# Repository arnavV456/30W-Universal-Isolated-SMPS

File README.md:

# Universal Isolated SMPS

A **30W isolated AC-DC flyback power supply** designed in **KiCad 9**, capable of converting a universal mains input into regulated isolated DC outputs.

This project implements a complete offline SMPS including EMI filtering, surge protection, isolated feedback, custom transformer footprint creation, PCB layout, 3D visualization, and manufacturing outputs.

---

# PCB Top

---

# PCB Bottom

---

## Specifications

| Parameter | Value |
|-----------|-------|
| Input Voltage | 85–265 VAC |
| Output 1 | 12V @ 2.5A |
| Output Power | 30W |
| Isolation | 4 kV |
| Topology | Flyback |
| Controller IC | TOP244Y |
| Transformer | MYRRA 74030 |
| PCB Layers | 2 |

---

# Features

- Universal AC input (85–265 VAC)
- Fully isolated flyback topology
- Reinforced 4 kV isolation
- TOP244Y integrated PWM controller
- Custom MYRRA 74030 transformer footprint & symbol
- EMI input filter
- MOV surge protection
- Fuse protection
- Common-mode choke
- X-Class capacitor
- Y-Class safety capacitor
- Primary RCD snubber network
- Secondary RC snubber
- Schottky output rectification
- Auxiliary transformer winding for controller bias
- Optocoupler-based isolated voltage feedback
- LC output filtering
- High-current PCB routing
- Separate primary and secondary ground planes
- 3D PCB model
- Manufacturing-ready Gerber generation

---

# Functional Overview

### AC Input Stage
- Universal AC input
- Fuse protection
- MOV surge suppressor
- Common-mode choke
- X and Y safety capacitors for EMI suppression

### High Voltage DC Bus
- Full bridge rectifier
- Bulk electrolytic capacitor for DC filtering

### Flyback Converter
- TOP244Y offline switching controller
- MYRRA 74030 flyback transformer
- Auxiliary winding for self-powered operation

### Protection Networks
- Primary RCD snubber to clamp transformer leakage spikes
- Secondary RC snubber to reduce ringing and EMI

### Output Stage
- MBR1060 Schottky rectifier
- LC output filter
- Low ripple 12V output

### Feedback Network
- LTV817A optocoupler
- Zener reference network
- Closed-loop isolated voltage regulation

### Additional Output
- Buck converter generating regulated 5V rail from the 12V output

---

# PCB Design Highlights

- Two-layer PCB
- Custom transformer footprint
- Custom transformer schematic symbol
- Wide power traces for high-current paths
- Dedicated primary HV_RETURN copper pour
- Dedicated secondary return plane
- Isolation barrier between primary and secondary
- Creepage and clearance maintained across isolation boundary
- Optimized placement for reduced switching loop area

---

# Schematic

---

# Repository Structure

```
Hardware/
├── universal_30w_smps.kicad_pro
├── universal_30w_smps.kicad_sch
├── universal_30w_smps.kicad_pcb
└── MYRRA.pretty/

Manufacturing/
├── Gerbers
└── Drill Files

Images/
├── PCB_Front.png
├── PCB_Back.png
└── schematic.png

3D Models/

README.md
```

---

# Design Tools

- KiCad 9
- Custom KiCad Libraries
- Git & GitHub

---

# Future Improvements

- Thermal analysis
- Efficiency characterization
- EMI compliance testing
- Hardware validation
- Oscilloscope waveform measurements
- Short-circuit and overload testing

---

## Author

**Arnav Verma**

Electronics & Computer Engineering

Embedded Systems • PCB Design • Power Electronics • IoT • STM32 • ESP32

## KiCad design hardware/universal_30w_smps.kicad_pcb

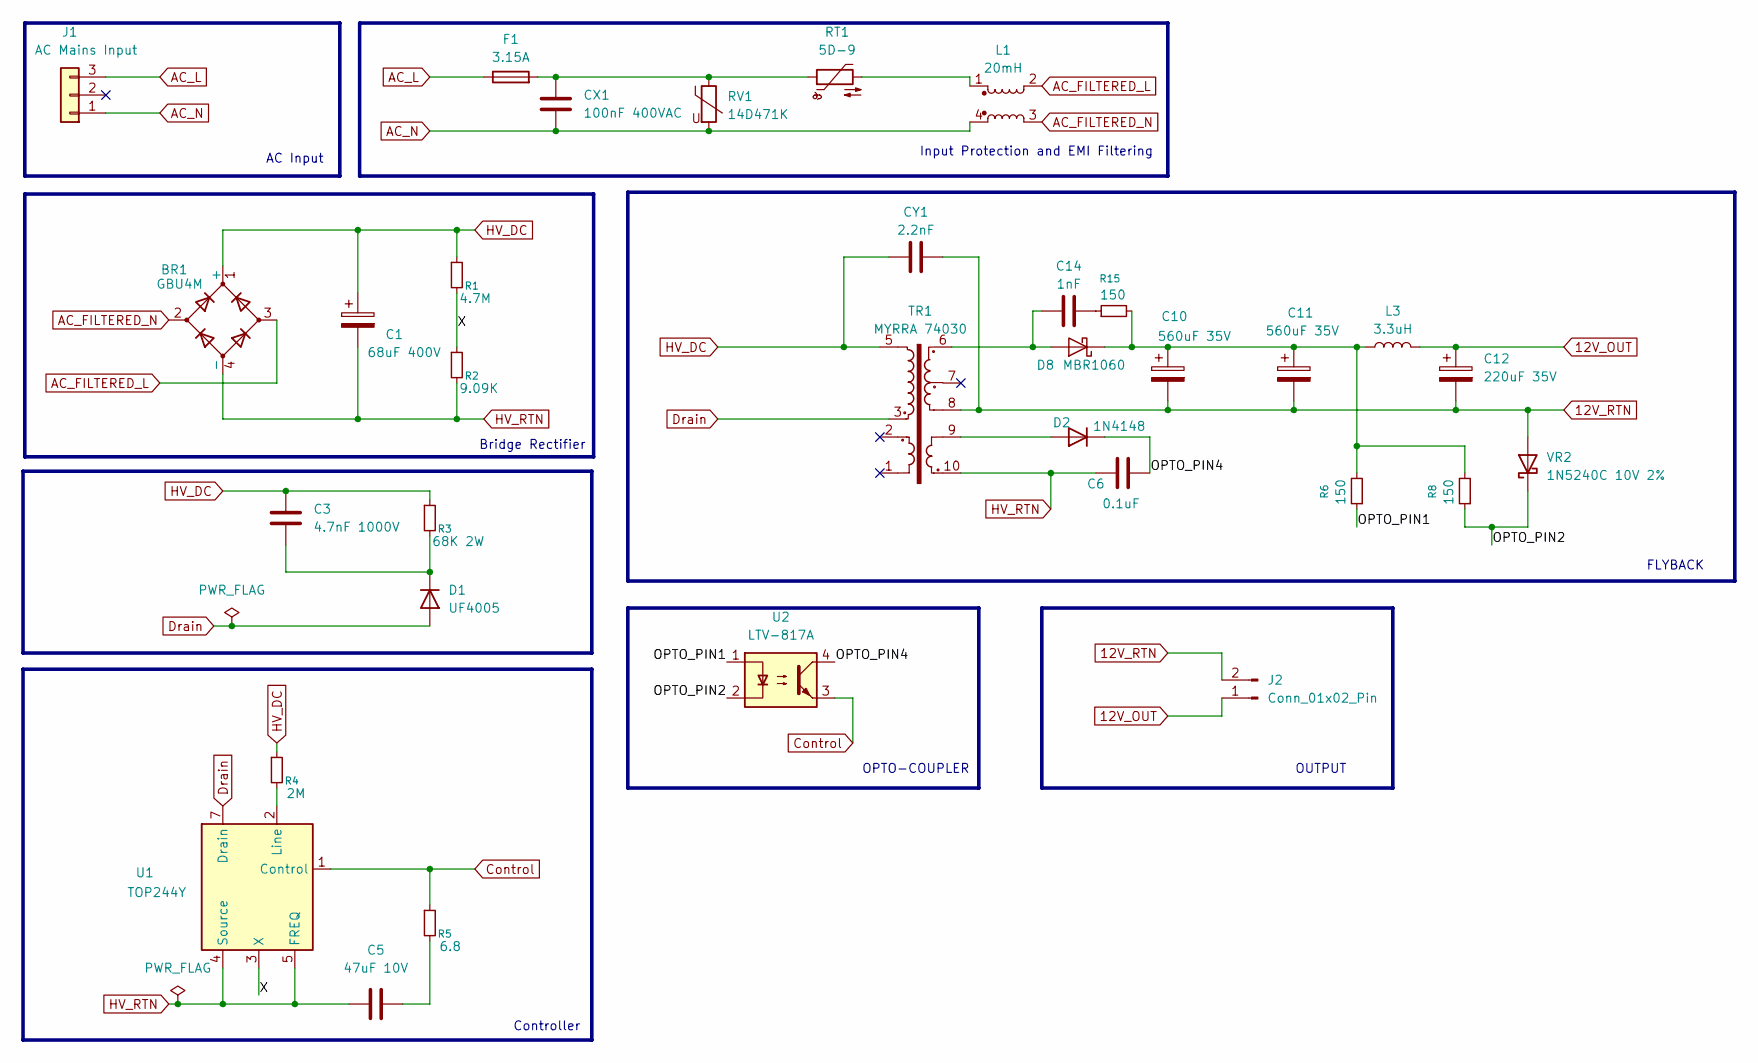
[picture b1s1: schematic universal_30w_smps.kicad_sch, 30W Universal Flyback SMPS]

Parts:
BR1: GBU4M; Diode_Bridge_Vishay_GBU
C1: 68uF 400V; CP_Radial_D18.0mm_P7.50mm
C3: 4.7nF 1000V; C_Rect_L11.0mm_W4.2mm_P10.00mm_MKT
C5: 47uF 10V; C_Radial_D6.3mm_H5.0mm_P2.50mm
C6: 0.1uF; C_Disc_D5.0mm_W2.5mm_P5.00mm
C10, C11: 560uF 35V; C_Disc_D5.0mm_W2.5mm_P5.00mm
C12: 220uF 35V; C_Radial_D10.0mm_H20.0mm_P5.00mm
C14: 1nF; C_Disc_D5.0mm_W2.5mm_P5.00mm
CX1: 100nF 400VAC; C_Rect_L18.0mm_W11.0mm_P15.00mm_FKS3_FKP3
CY1: 2.2nF; C_Disc_D7.5mm_W5.0mm_P10.00mm
D1: UF4005; D_DO-41_SOD81_P10.16mm_Horizontal
D2: 1N4148; D_DO-35_SOD27_P7.62mm_Horizontal
D8: MBR1060; D_SOD-123F
F1: 3.15A; Fuseholder_Cylinder-5x20mm_Stelvio-Kontek_PTF78_Horizontal_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
J1: AC Mains Input; TerminalBlock_Phoenix_MKDS-1,5-3-5.08_1x03_P5.08mm_Horizont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
J2: Conn_01x02_Pin; TerminalBlock_Phoenix_MKDS-1,5-2-5.08_1x02_P5.08mm_Horizont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
L1: 20mH; L_CommonModeChoke_Bourns_SRF1260
L3: 3.3uH; L_Radial_D10.0mm_P5.00mm_Fastron_07P
R1: 4.7M; R_Axial_DIN0207_L6.3mm_D2.5mm_P10.16mm_Horizontal
R2: 9.09K; R_Axial_DIN0207_L6.3mm_D2.5mm_P10.16mm_Horizontal
R3: 68K 2W; R_Axial_DIN0414_L11.9mm_D4.5mm_P15.24mm_Horizontal
R4: 2M; R_Axial_DIN0207_L6.3mm_D2.5mm_P10.16mm_Horizontal
R5: 6.8; R_Axial_DIN0207_L6.3mm_D2.5mm_P10.16mm_Horizontal
R6, R8, R15: 150; R_Axial_DIN0207_L6.3mm_D2.5mm_P10.16mm_Horizontal
RT1: 5D-9; RV_Disc_D9mm_W4.2mm_P5mm
RV1: 14D471K; RV_Disc_D15.5mm_W4mm_P7.5mm
TR1: MYRRA 74030; Transformer_Myrra_74030_Horizontal
U1: TOP244Y; TO-220-7_P2.54x3.8mm_StaggerOdd_Lead5.85mm_TabDown
U2: LTV-817A; DIP-4_W7.62mm
VR2: 1N5240C 10V 2%; D_DO-41_SOD81_P10.16mm_Horizontal

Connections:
12V_OUT: C12.1, J2.1, L3.2
12V_RTN: C10.2, C11.2, C12.2, CY1.2, J2.2, TR1.8, VR2.2 (A)
/OPTO_PIN1: R6.1, U2.1
/OPTO_PIN2: R8.1, U2.2, VR2.1 (K)
/OPTO_PIN4: C6.2, D2.1 (K), U2.4
/X: R1.2, R2.1, U1.3 (X)
AC_FILTERED_L: BR1.3, L1.2
AC_FILTERED_N: BR1.2, L1.3
AC_L: F1.1, J1.3
AC_N: CX1.2, J1.1, L1.4, RV1.2
Control: R5.1, U1.1 (Control), U2.3
Drain: D1.2 (A), TR1.3, U1.7 (Drain)
HV_DC: BR1.1 (+), C1.1, C3.1, CY1.1, R1.1, R3.1, R4.1, TR1.5
HV_RTN: BR1.4 (-), C1.2, C5.1, C6.1, R2.2, TR1.10, U1.4 (Source), U1.5 (FREQ)
unnamed: C5.2, R5.2
unnamed: C14.2, R15.1
unnamed: CX1.1, F1.2, RT1.1, RV1.1
unnamed: C3.2, D1.1 (K), R3.2
unnamed: D2.2 (A), TR1.9
unnamed: C14.1, D8.2 (A), TR1.6
unnamed: C10.1, C11.1, D8.1 (K), L3.1, R6.2, R8.2, R15.2
unnamed: L1.1, RT1.2
unnamed: R4.2, U1.2 (Line)

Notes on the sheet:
OUTPUT
FLYBACK
OPTO-COUPLER
Input Protection and EMI Filtering
Bridge Rectifier
AC Input
Controller

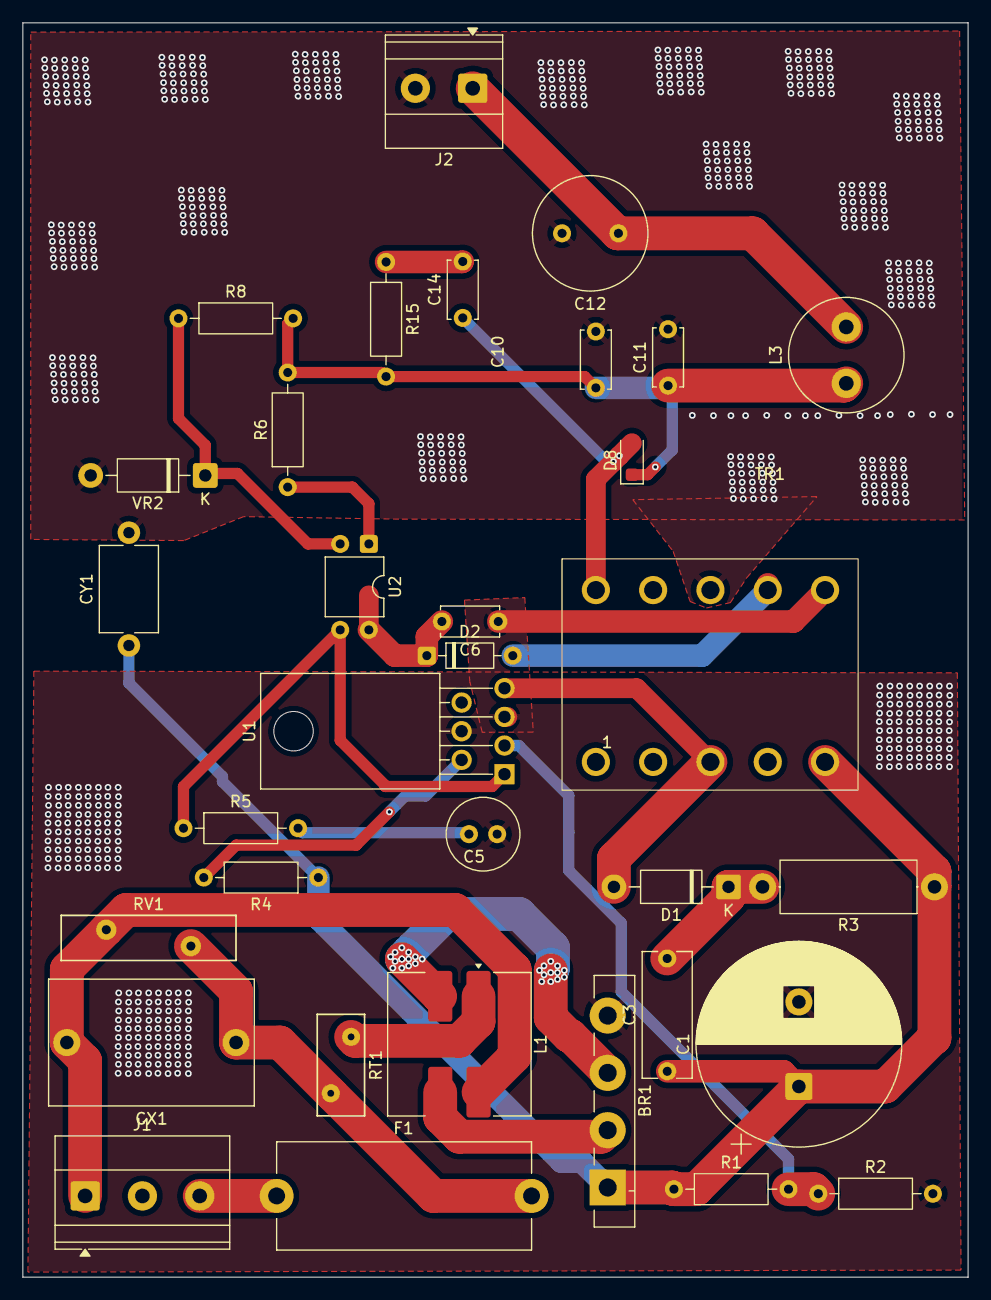
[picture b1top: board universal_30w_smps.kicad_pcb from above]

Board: 2 copper layers, 83.8 x 111.2 mm, 33 parts (0 on the bottom side), 23 nets.
